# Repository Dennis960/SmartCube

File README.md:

# SmartCube

SmartCube is a modular, connectable LED cube platform. Each module is a small PCB containing addressable LEDs and sensors; modules mechanically and electrically connect using pogo pins and neodymium magnets. This monorepo contains KiCad PCB sources, a CadQuery 3D-model generator (that uses KiCad STEP exports), and firmware for the microcontrollers used across modules.

<!-- 

TODO: Add image, once the cubes arrive -->

## Key features

- Modular PCB-based cube modules with addressable LEDs and Hall sensors
- Electrical connection via pogo pins; mechanical coupling via neodymium magnets
- ESP32 used as a power/aggregation/controller cube
- PY32 microcontrollers used for individual LED modules
- CadQuery scripts that generate printable enclosures using KiCad STEP references

## Project Structure

- [PCB](./PCB): KiCad projects for the LED module, power supply module and pogo pin connectors, as well as helper scripts for panelization.

- [3DModel](./3DModel): CadQuery scripts to generate 3D models of the cube modules and enclosures, using KiCad STEP exports as references.

- [Firmware](./Firmware): CMake-based firmware for the PY32 microcontrollers used in the LED modules, with support for flashing via ST-Link and esp-idf-based firmware for the ESP32 power/controller module.

A devcontainer exists for development for the 3DModel and panelization.

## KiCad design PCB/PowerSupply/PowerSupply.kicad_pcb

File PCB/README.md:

# PCB

This folder contains the KiCad projects for the SmartCube LED module, power supply module, and pogo pin connectors. It also includes helper scripts for panelization of the PCBs for manufacturing.

The KiCad projects all use the same shared library located in the `libs` folder.

If having problems loading footprints or 3d models, make sure to add the symbol and CustomFootprints libraries in KiCad.

## Module

[./Module](./Module) contains the KiCad project for the main LED module PCB.

It includes addressable LEDs and Hall sensors.
Communication happens via PY32 microcontrollers using pogo pin connectors.

## Power Module

[./PowerModule](./PowerModule) contains the KiCad project for the power supply module PCB.

It provides 5V power to the cubes via pogo pin connectors.

At least one power module is required in a SmartCube assembly to provide power to the other modules.

## Pogo Pin Connectors

[./PogoConnectors](./PogoConnectors) contains the KiCad projects for the pogo pin connectors.

It is used to connect the modules both mechanically and electrically.

## Panelization

[./Panel](./Panel) contains scripts to panelize the PCBs for manufacturing. The panelization uses the kikit tool.

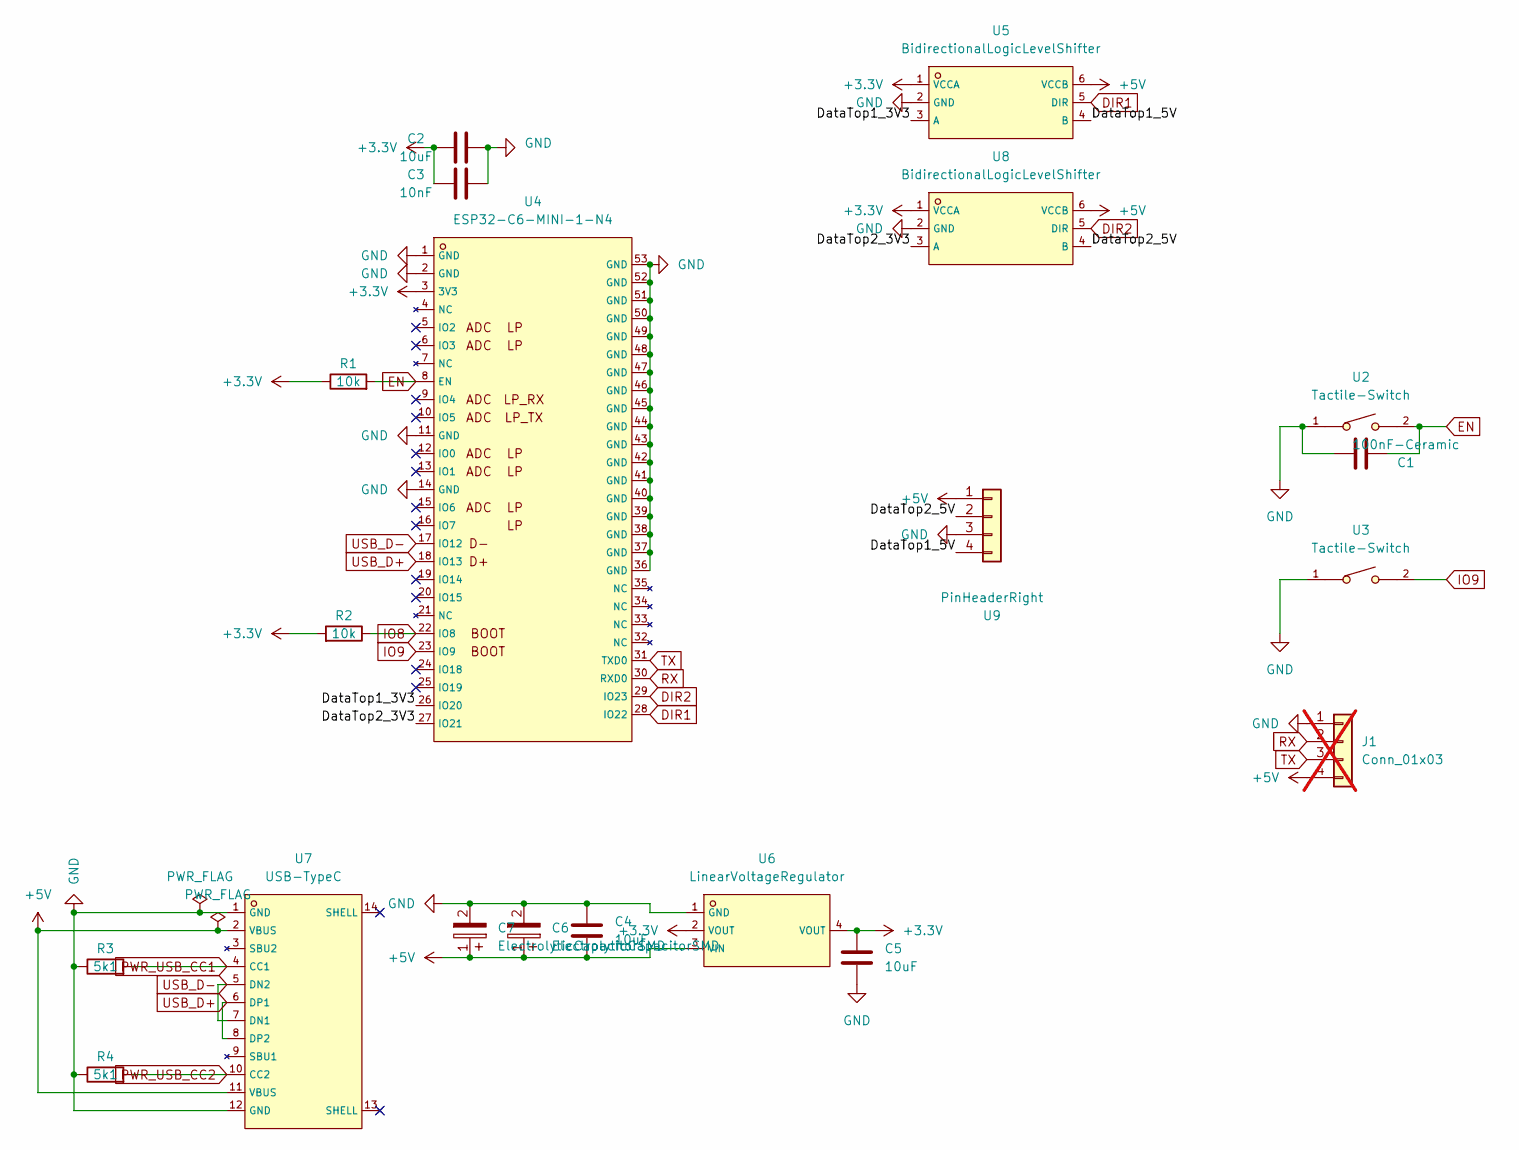
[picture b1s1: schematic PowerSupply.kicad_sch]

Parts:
C1: 100nF-Ceramic; C_0402_1005Metric; MPN C1525; LCSC C1525
C2: 10uF; C_0603_1608Metric; MPN C15525; LCSC C19702
C3: 10nF; C_0402_1005Metric; MPN C15195; LCSC C15195
C4, C5: 10uF; C_0603_1608Metric; LCSC C19702
C6, C7: ElectrolyticCapacitorSMD; CAP-SMD_BD6.3-L6.6-W6.6-FD; LCSC C335982
J1: Conn_01x03; PinHeader_1x04_P2.54mm_Vertical; MPN /; not fitted
R1, R2: 10k; R_0402_1005Metric; MPN C25744; LCSC C25744
R3, R4: 5k1; R_0402_1005Metric; MPN C25905; LCSC C25905
U2, U3: Tactile-Switch; Button; MPN C720477; LCSC C720477
U4: ESP32-C6-MINI-1-N4; ESP32C6-Mini-1-N4; LCSC C5736265
U5, U8: BidirectionalLogicLevelShifter; BidirectionalLogicLevelConverter; LCSC C168855
U6: LinearVoltageRegulator; VoltageRegulator; LCSC C6186
U7: USB-TypeC; USB-C-SMD_TYPE-C-6PIN-2MD-073; LCSC C2765186
U9: PinHeaderRight; 01x04_PinPads; LCSC C492414

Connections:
+3.3V: C2.1, C3.1, C5.1, R1.1, R2.2, U4.3 (3V3), U5.1 (VCCA), U6.2 (VOUT), U6.4 (VOUT), U8.1 (VCCA)
+5V: C4.2, C6.1, C7.1, J1.4, U5.6 (VCCB), U6.3 (VIN), U7.2 (VBUS), U7.11 (VBUS), U8.6 (VCCB), U9.1
/DataTop1_3V3: U4.26 (IO20), U5.3 (A)
/DataTop1_5V: U5.4 (B), U9.4
/DataTop2_3V3: U4.27 (IO21), U8.3 (A)
/DataTop2_5V: U8.4 (B), U9.2
DIR1: U4.28 (IO22), U5.5 (DIR)
DIR2: U4.29 (IO23), U8.5 (DIR)
EN: C1.1, R1.2, U2.2, U4.8 (EN)
GND: C1.2, C2.2, C3.2, C4.1, C5.2, C6.2, C7.2, J1.1, R3.1, R4.1, U2.1, U3.1, U4.1 (GND), U4.2 (GND), U4.11 (GND), U4.14 (GND), U4.36 (GND), U4.37 (GND), U4.38 (GND), U4.39 (GND), U4.40 (GND), U4.41 (GND), U4.42 (GND), U4.43 (GND), U4.44 (GND), U4.45 (GND), U4.46 (GND), U4.47 (GND), U4.48 (GND), U4.49 (GND), U4.50 (GND), U4.51 (GND), U4.52 (GND), U4.53 (GND), U5.2 (GND), U6.1 (GND), U7.1 (GND), U7.12 (GND), U8.2 (GND), U9.3
IO8: R2.1, U4.22 (IO8)
IO9: U3.2, U4.23 (IO9)
PWR_USB_CC1: R3.2, U7.4 (CC1)
PWR_USB_CC2: R4.2, U7.10 (CC2)
RX: J1.2, U4.30 (RXD0)
TX: J1.3, U4.31 (TXD0)
USB_D+: U4.18 (IO13), U7.6 (DP1), U7.8 (DP2)
USB_D-: U4.17 (IO12), U7.5 (DN2), U7.7 (DN1)

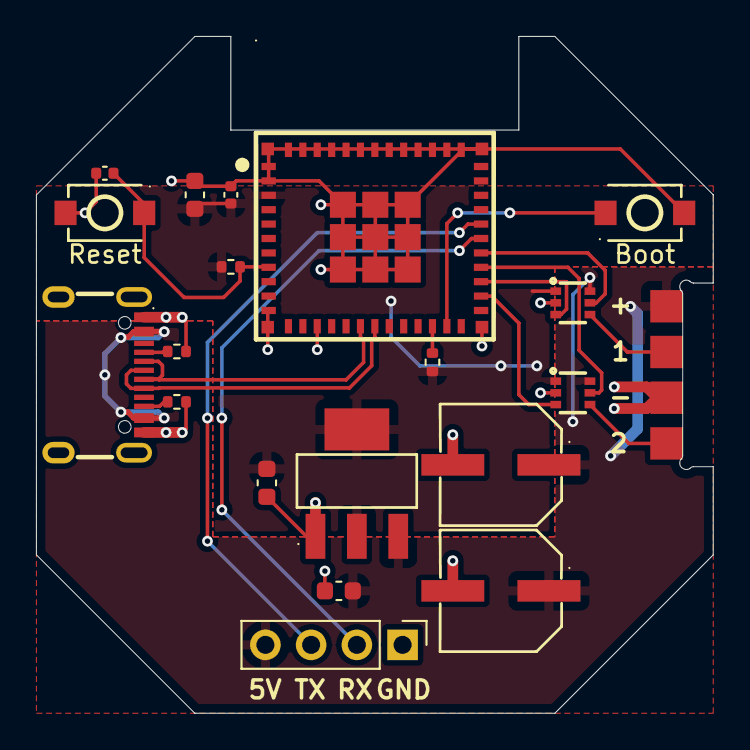
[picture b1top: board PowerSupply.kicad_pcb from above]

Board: 2 copper layers, 37.6 x 37.6 mm, 20 parts (0 on the bottom side), 18 nets.

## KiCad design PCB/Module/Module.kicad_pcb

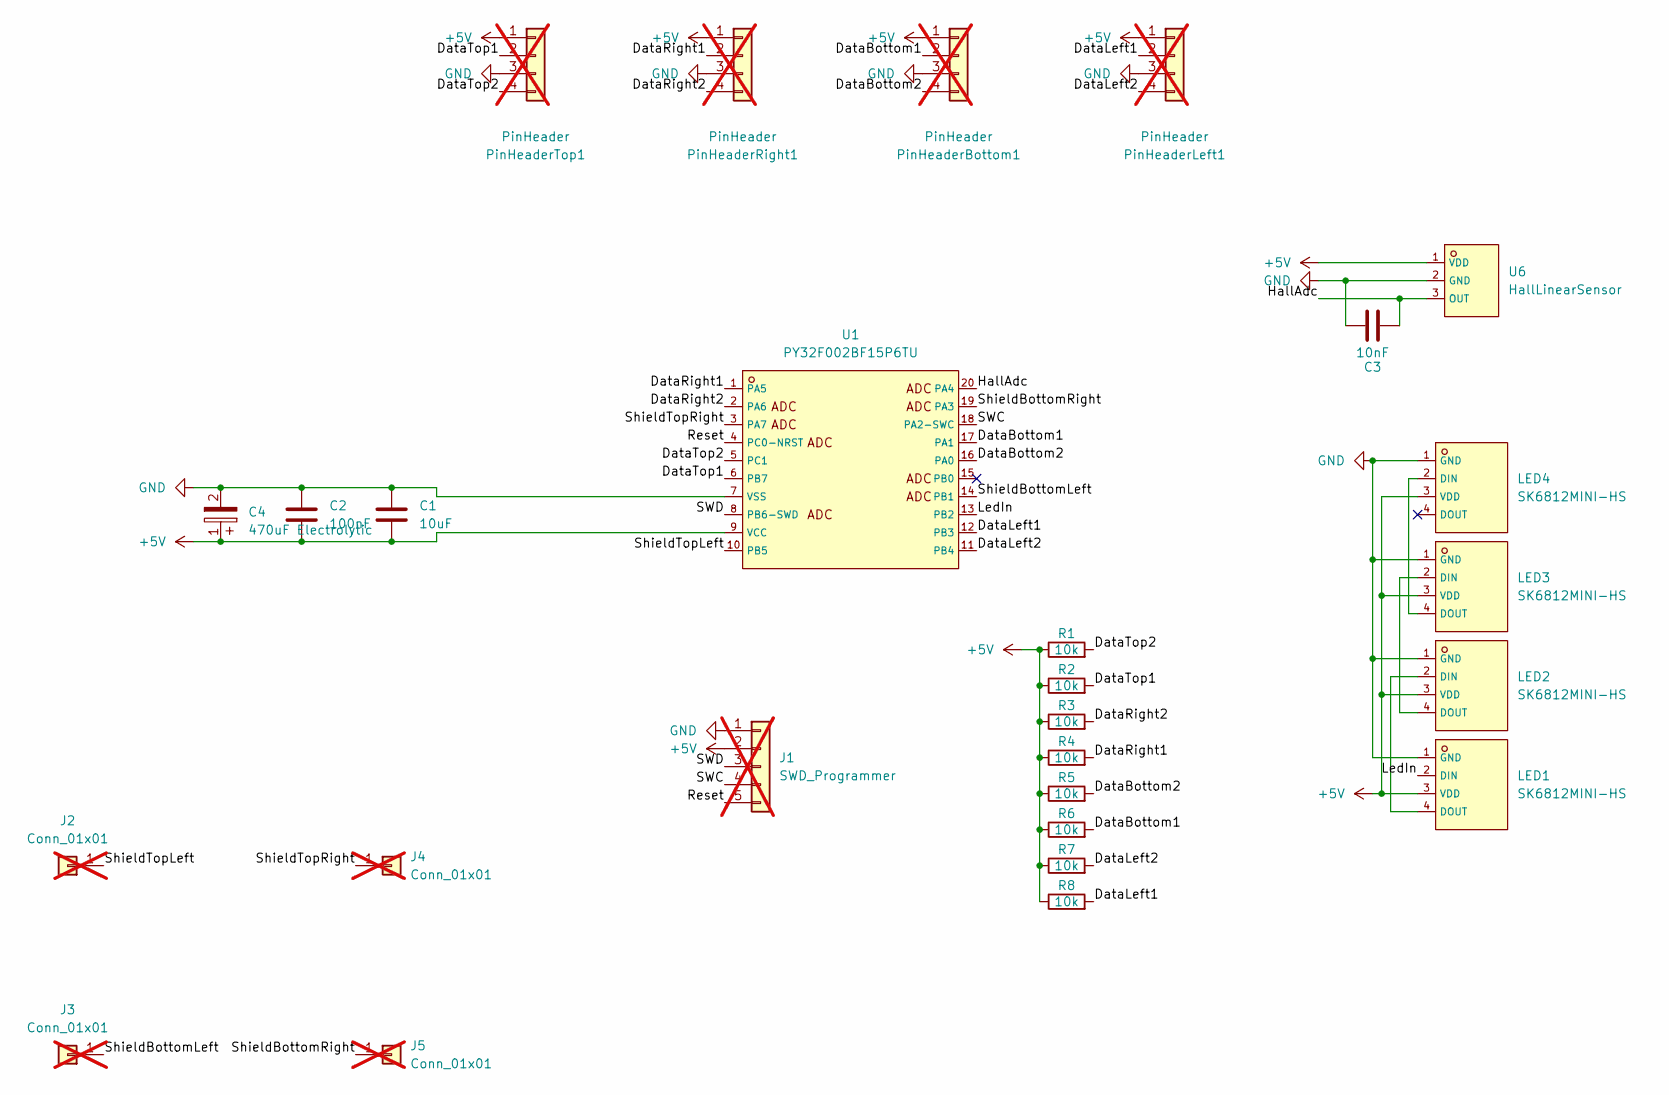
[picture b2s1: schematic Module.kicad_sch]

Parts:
C1: 10uF; C_0603_1608Metric; LCSC C19702
C2: 100nF; C_0402_1005Metric; LCSC C1525
C3: 10nF; C_0402_1005Metric; LCSC C15195
C4: 470uF Electrolytic; CAP-SMD_BD6.3-L6.6-W6.6-FD; LCSC C335982
J1: SWD_Programmer; SWD_Pad; not fitted
J2, J3, J4, J5: Conn_01x01; ShieldConnector; not fitted
LED1, LED2, LED3, LED4: SK6812MINI-HS; LED-SK6812MINI-HS; LCSC C2922787
PinHeaderBottom1: PinHeader; 01x04_PinPads; LCSC C492414; not fitted
PinHeaderLeft1: PinHeader; 01x04_PinPads; LCSC C492414; not fitted
PinHeaderRight1: PinHeader; 01x04_PinPads; LCSC C492414; not fitted
PinHeaderTop1: PinHeader; 01x04_PinPads; LCSC C492414; not fitted
R1, R2, R3, R4, R5, R6, R7, R8: 10k; R_0402_1005Metric; LCSC C25744
U1: PY32F002BF15P6TU; Py32; LCSC C7469098
U6: HallLinearSensor; LCSC C7420984

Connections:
+5V: C1.2, C2.2, C4.1, J1.2, LED1.3 (VDD), LED2.3 (VDD), LED3.3 (VDD), LED4.3 (VDD), PinHeaderBottom1.1, PinHeaderLeft1.1, PinHeaderRight1.1, PinHeaderTop1.1, R1.1, R2.1, R3.1, R4.1, R5.1, R6.1, R7.1, R8.1, U1.9 (VCC), U6.1 (VDD)
/DataBottom1: PinHeaderBottom1.2, R6.2, U1.17 (PA1)
/DataBottom2: PinHeaderBottom1.4, R5.2, U1.16 (PA0)
/DataLeft1: PinHeaderLeft1.2, R8.2, U1.12 (PB3)
/DataLeft2: PinHeaderLeft1.4, R7.2, U1.11 (PB4)
/DataRight1: PinHeaderRight1.2, R4.2, U1.1 (PA5)
/DataRight2: PinHeaderRight1.4, R3.2, U1.2 (PA6)
/DataTop1: PinHeaderTop1.2, R2.2, U1.6 (PB7)
/DataTop2: PinHeaderTop1.4, R1.2, U1.5 (PC1)
/HallAdc: C3.2, U1.20 (PA4), U6.3 (OUT)
/LedIn: LED1.2 (DIN), U1.13 (PB2)
/Reset: J1.5, U1.4 (PC0-NRST)
/SWC: J1.4, U1.18 (PA2-SWC)
/SWD: J1.3, U1.8 (PB6-SWD)
/ShieldBottomLeft: J3.1, U1.14 (PB1)
/ShieldBottomRight: J5.1, U1.19 (PA3)
/ShieldTopLeft: J2.1, U1.10 (PB5)
/ShieldTopRight: J4.1, U1.3 (PA7)
GND: C1.1, C2.1, C3.1, C4.2, J1.1, LED1.1 (GND), LED2.1 (GND), LED3.1 (GND), LED4.1 (GND), PinHeaderBottom1.3, PinHeaderLeft1.3, PinHeaderRight1.3, PinHeaderTop1.3, U1.7 (VSS), U6.2 (GND)
unnamed: LED1.4 (DOUT), LED2.2 (DIN)
unnamed: LED2.4 (DOUT), LED3.2 (DIN)
unnamed: LED3.4 (DOUT), LED4.2 (DIN)

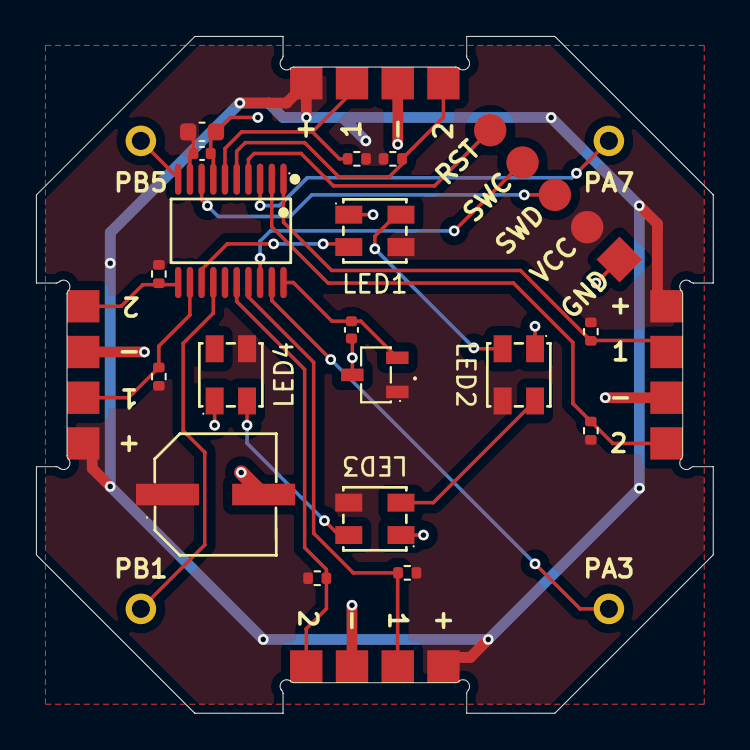
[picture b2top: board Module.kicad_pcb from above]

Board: 2 copper layers, 37.6 x 37.6 mm, 27 parts (0 on the bottom side), 22 nets.

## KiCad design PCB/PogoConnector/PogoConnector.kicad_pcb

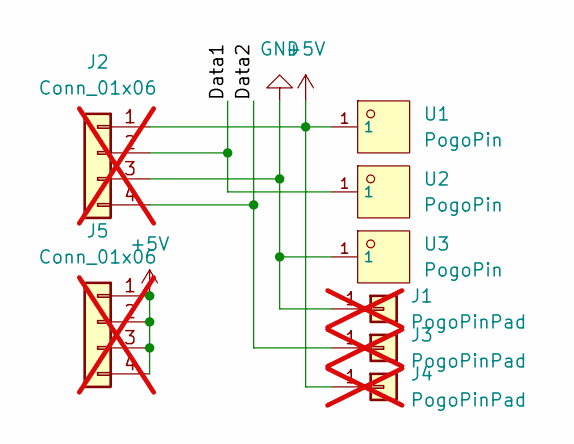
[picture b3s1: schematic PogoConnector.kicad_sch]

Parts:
J1, J3, J4: PogoPinPad; not fitted
J2, J5: Conn_01x06; 01x04_PinPads_Single; not fitted
U1, U2, U3: PogoPin; LCSC C2988082

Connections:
+5V: J2.1, J4.1, J5.1, J5.2, J5.3, J5.4, U1.1
/Data1: J2.2, U2.1
/Data2: J2.4, J3.1
GND: J1.1, J2.3, U3.1

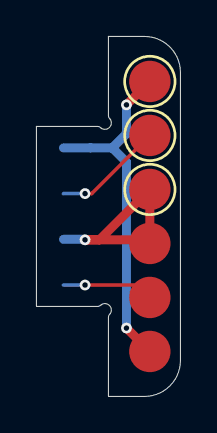
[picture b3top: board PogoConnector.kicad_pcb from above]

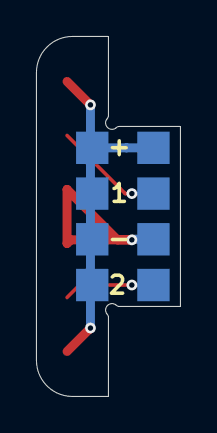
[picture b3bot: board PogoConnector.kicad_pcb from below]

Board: 2 copper layers, 8.0 x 20.0 mm, 8 parts (2 on the bottom side), 4 nets.

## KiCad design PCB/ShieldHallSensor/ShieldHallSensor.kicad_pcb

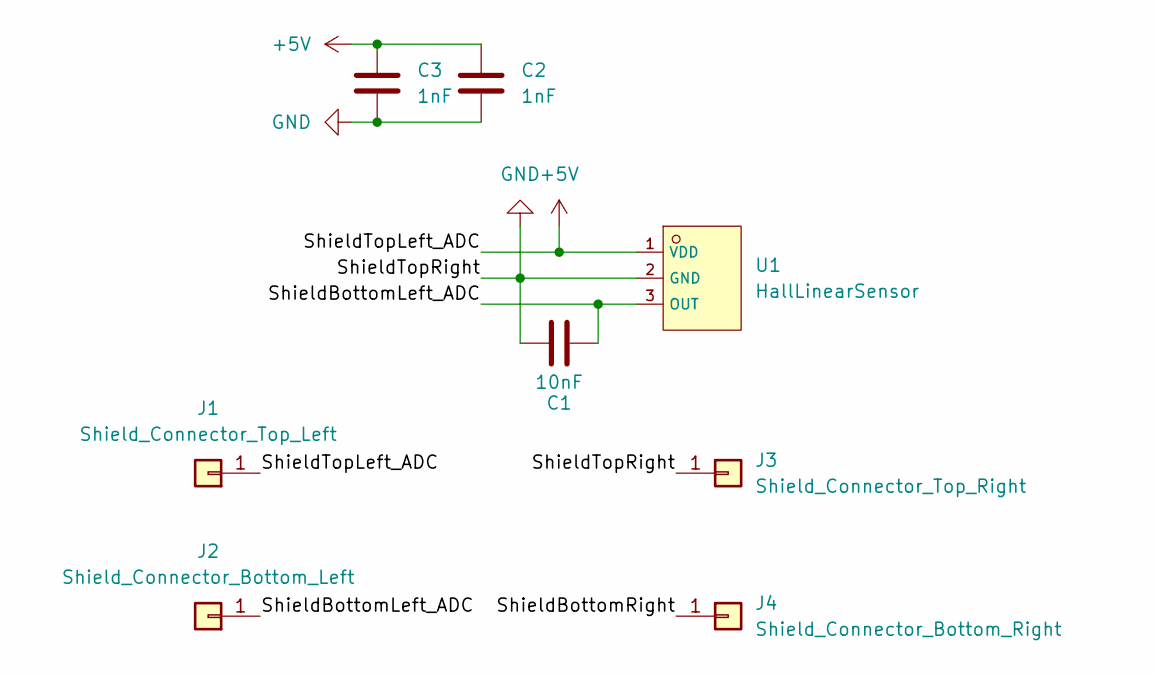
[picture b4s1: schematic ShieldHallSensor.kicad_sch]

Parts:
C1: 10nF; C_0402_1005Metric
C2, C3: 1nF; C_0402_1005Metric
J1: Shield_Connector_Top_Left; HDR-TH_1P-V-F-1; LCSC C2883469
J2: Shield_Connector_Bottom_Left; HDR-TH_1P-V-F-1; LCSC C2883469
J3: Shield_Connector_Top_Right; HDR-TH_1P-V-F-1; LCSC C2883469
J4: Shield_Connector_Bottom_Right; HDR-TH_1P-V-F-1; LCSC C2883469
U1: HallLinearSensor; LCSC C7420984

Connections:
+5V: C2.1, C3.1, J1.1, U1.1 (VDD)
/ShieldBottomLeft_ADC: C1.2, J2.1, U1.3 (OUT)
/ShieldBottomRight: J4.1
GND: C1.1, C2.2, C3.2, J3.1, U1.2 (GND)

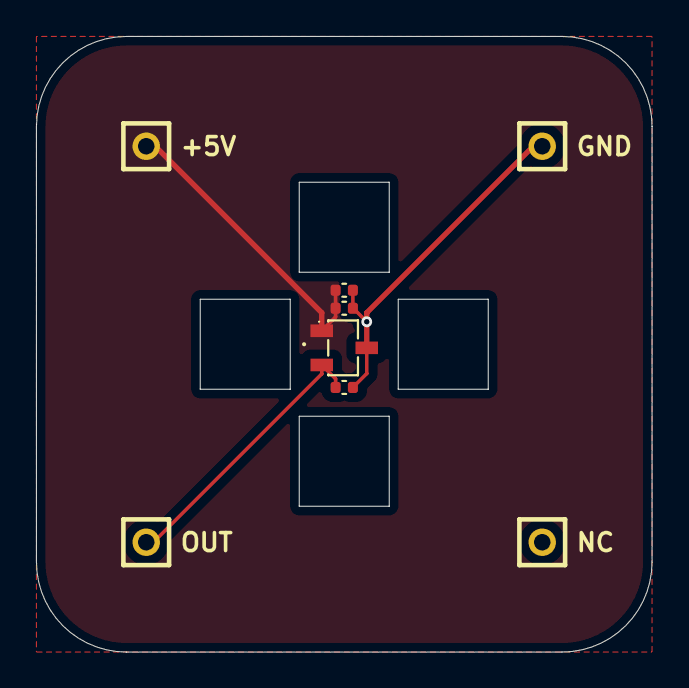
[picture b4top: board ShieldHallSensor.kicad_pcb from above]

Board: 2 copper layers, 34.2 x 34.2 mm, 8 parts (0 on the bottom side), 3 nets.
